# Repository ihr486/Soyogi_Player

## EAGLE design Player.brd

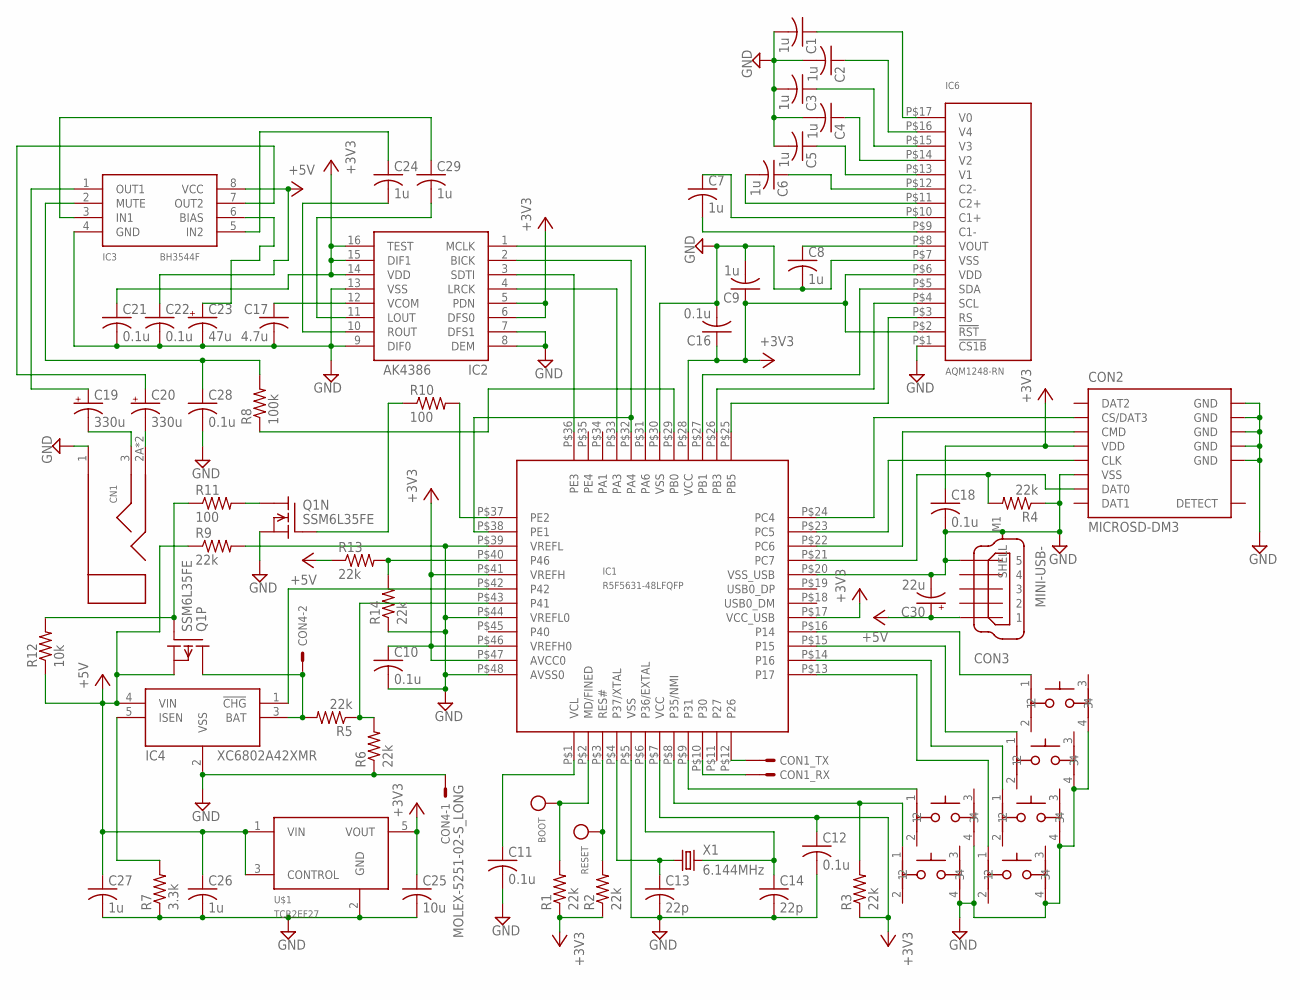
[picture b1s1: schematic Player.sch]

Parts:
BOOT: CHECK_PIN; SLC-22-G
C1, C2, C3, C4, C5, C6, C7, C8, C9, C24, C26, C27, C29: 1u; 2012-C
C10, C11, C12, C16, C18, C21, C22, C28: 0.1u; 2012-C
C13, C14: 22p; 1608
C17: 4.7u; 2012-C
C19, C20: 330u; E2,5-8
C23: 47u; E2,5-8
C25: 10u; 3216
C30: 22u; E2,5-8
CN1: STEREO-3.5-MJ8435; MJ8435
CON1: UART-S; IL-G-04-S
CON2: MICROSD-DM3; DM3AT-SF-PEJ
CON3: MINI-USB-; UX60A-MB-5ST
CON4: MOLEX-5251-02-S_LONG; 5251-02-S_LONG
IC1: R5F5631-48LFQFP; P-LFQFP48-7X7-0.50
IC2: AK4386; TSSOP16
IC3: BH3544F; SOIC8
IC4: XC6802A42XMR; SOT23-5
IC6: AQM1248-RN; AQM1248A-RN
Q1: SSM6L35FE; 2-2N1D
R1, R2, R3, R4, R5, R6, R9, R13, R14: 22k; 2012-R
R7: 3.3k; 2012-R
R8: 100k; 2012-R
R10, R11: 100; 2012-R
R12: 10k; 2012-R
RESET: CHECK_PIN; SLC-22-G
SW1, SW2, SW3, SW4, SW5, SW6: PUSHSW
U$1: TCR2EF27; 5-LEAD_TSOT
X1: 6.144MHz; TINYCRYSTAL

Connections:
+3V3: C9.1, C10.1, C12.1, C16.1, C18.1, C21.1, C25.1, CON2.4 (VDD), IC1.P$7 (VCC), IC1.P$17 (VCC_USB), IC1.P$28 (VCC), IC1.P$41 (VREFH), IC1.P$46 (VREFH0), IC1.P$47 (AVCC0), IC2.5 (PDN), IC2.6 (DFS0), IC2.14 (VDD), IC2.15 (DIF1), IC2.16 (TEST), IC6.P$2 (!RST), IC6.P$6 (VDD), R1.1, R2.1, R3.1, U$1.5 (VOUT)
+5V: C22.1, C26.1, C27.1, C30.+, CON3.1, IC3.8 (VCC), IC4.4 (VIN), Q1.4 (S), R9.1, R12.1, R13.1, U$1.1 (VIN), U$1.3 (CONTROL)
GND: C1.2, C2.2, C3.2, C4.2, C5.2, C8.2, C9.2, C10.2, C11.2, C12.2, C13.2, C14.2, C16.2, C17.2, C18.2, C21.2, C22.2, C23.-, C25.2, C26.2, C27.2, C28.2, C30.-, CN1.1 (SLEEVE), CON1.1 (GND), CON2.6 (VSS), CON2.SHELL1 (GND), CON2.SHELL2 (GND), CON2.SHELL3 (GND), CON2.SHELL4 (GND), CON2.SHELL5 (GND), CON3.5, CON3.M1 (SHELL), CON4.1, IC1.P$5 (VSS), IC1.P$20 (VSS_USB), IC1.P$30 (VSS), IC1.P$39 (VREFL), IC1.P$44 (VREFL0), IC1.P$48 (AVSS0), IC2.7 (DFS1), IC2.8 (DEM), IC2.9 (DIF0), IC2.13 (VSS), IC3.4 (GND), IC4.2 (VSS), IC6.P$1 (!CS1B), IC6.P$7 (VSS), Q1.1 (S), R4.1, R6.1, R7.1, R9.2, R14.1, SW1.4, SW2.4, SW3.4, SW4.4, SW5.4, SW6.4, U$1.2 (GND)
unnamed: C1.1, IC6.P$17 (V0)
unnamed: C2.1, IC6.P$16 (V4)
unnamed: C3.1, IC6.P$15 (V3)
unnamed: C4.1, IC6.P$14 (V2)
unnamed: C5.1, IC6.P$13 (V1)
unnamed: C11.1, IC1.P$1 (VCL)
unnamed: C6.1, IC6.P$12 (C2-)
unnamed: C6.2, IC6.P$11 (C2+)
unnamed: C7.1, IC6.P$10 (C1+)
unnamed: C7.2, IC6.P$9 (C1-)
unnamed: C8.1, IC6.P$8 (VOUT)
unnamed: CON1.3 (S), IC1.P$12 (P26)
unnamed: CON1.2 (S), IC1.P$10 (P30)
unnamed: IC1.P$9 (P31), SW2.1
unnamed: IC1.P$8 (P35/NMI), R3.2, SW1.1
unnamed: CON2.5 (CLK), IC1.P$23 (PC5)
unnamed: IC1.P$37 (PE2), R10.2
unnamed: Q1.2 (G), R10.1
unnamed: IC1.P$3 (RES#), R2.2, RESET.SIGNAL
unnamed: Q1.5 (G), R11.1, R12.2
unnamed: CON2.7 (DAT0), IC1.P$21 (PC7), R4.2
unnamed: BOOT.SIGNAL, IC1.P$2 (MD/FINED), R1.2
unnamed: IC1.P$16 (P14), SW6.1
unnamed: IC1.P$15 (P15), SW5.1
unnamed: IC1.P$14 (P16), SW4.1
unnamed: IC1.P$13 (P17), SW3.1
unnamed: CON2.3 (CMD), IC1.P$22 (PC6)
unnamed: CON2.2 (CS/DAT3), IC1.P$24 (PC4)
unnamed: C17.1, IC2.12 (VCOM)
unnamed: IC1.P$25 (PB5), IC6.P$3 (RS)
unnamed: IC1.P$26 (PB3), IC6.P$4 (SCL)
unnamed: IC1.P$27 (PB1), IC6.P$5 (SDA)
unnamed: C24.2, IC2.10 (ROUT)
unnamed: C29.2, IC2.11 (LOUT)
unnamed: C20.+, IC3.7 (OUT2)
unnamed: C23.+, IC3.6 (BIAS)
unnamed: C19.+, IC3.1 (OUT1)
unnamed: C19.-, CN1.3 (RING)
unnamed: C20.-, CN1.2A (TIP), CN1.2B (TIP)
unnamed: IC1.P$36 (PE3), IC2.3 (SDTI)
unnamed: IC1.P$31 (PA6), IC2.1 (MCLK)
unnamed: IC1.P$32 (PA4), IC1.P$38 (PE1), IC2.2 (BICK)
unnamed: IC1.P$33 (PA3), IC2.4 (LRCK)
unnamed: C24.1, IC3.5 (IN2)
unnamed: Q1.6 (D), R11.2
unnamed: IC1.P$43 (P41), R5.1, R6.2
unnamed: IC1.P$42 (P42), IC4.1 (!CHG!)
unnamed: CON4.2, IC4.3 (BAT), Q1.3 (D), R5.2
unnamed: C29.1, IC3.3 (IN1)
unnamed: IC4.5 (ISEN), R7.2
unnamed: C28.1, IC3.2 (MUTE), R8.2
unnamed: IC1.P$29 (PB0), R8.1
unnamed: IC1.P$40 (P46), R13.2, R14.2
unnamed: C13.1, IC1.P$4 (P37/XTAL), X1.1
unnamed: C14.1, IC1.P$6 (P36/EXTAL), X1.2
VCC: CON1.4 (VCC)

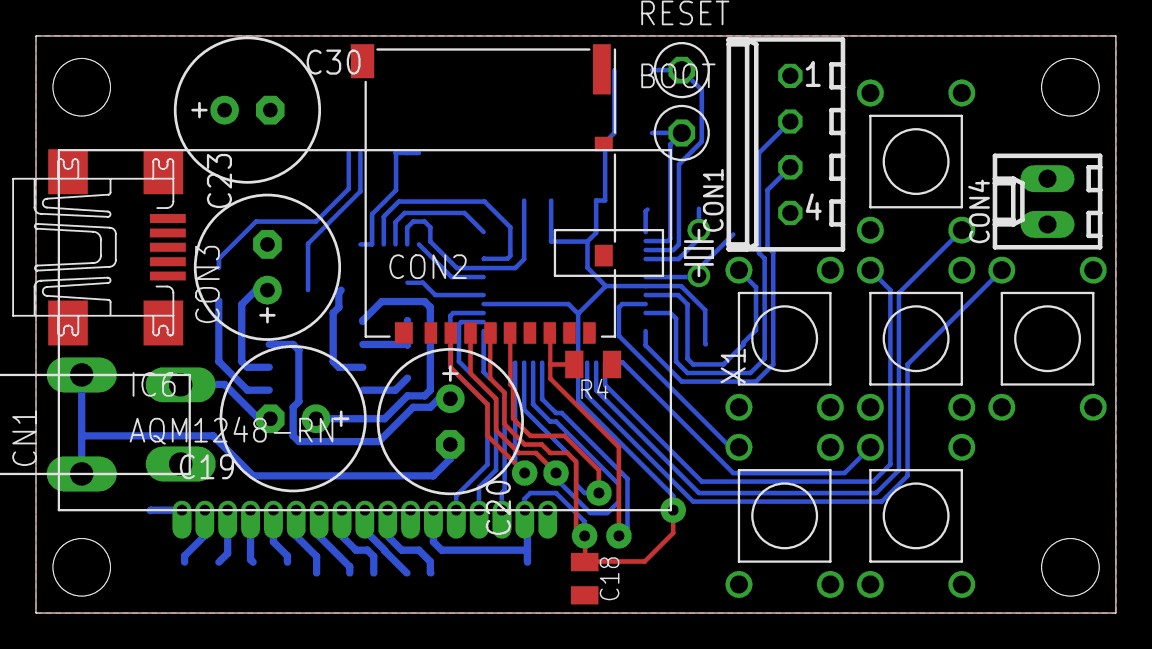
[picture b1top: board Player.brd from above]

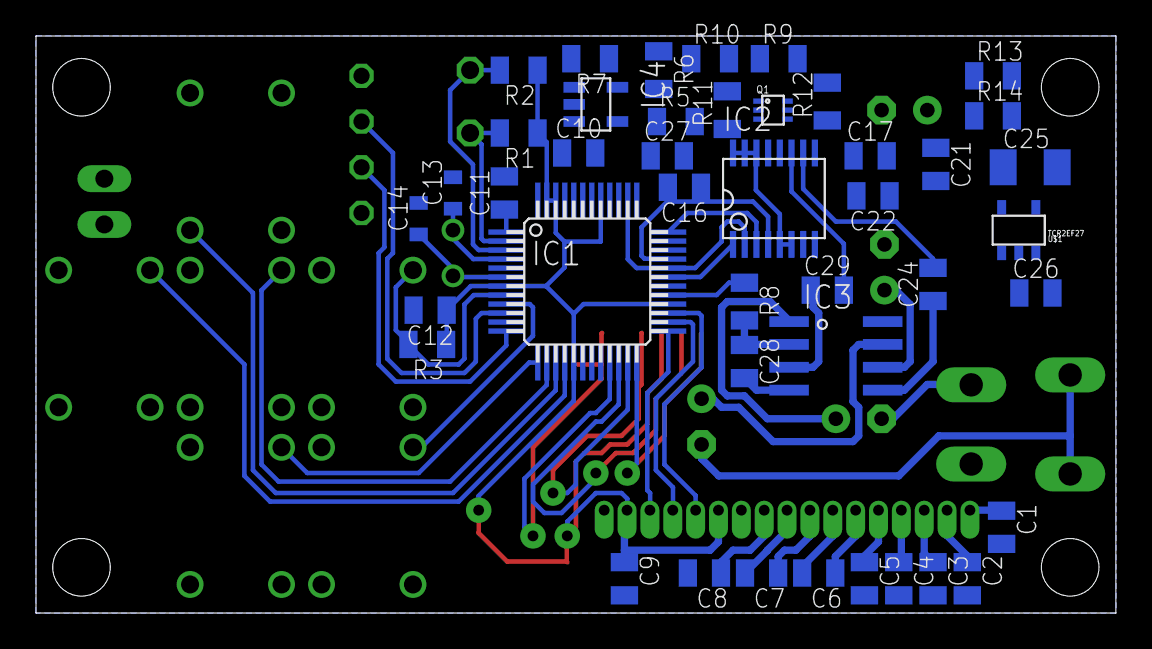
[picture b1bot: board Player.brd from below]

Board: 2 copper layers, 60.0 x 32.1 mm, 64 parts (43 on the bottom side), 58 nets.

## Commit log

2016-01-18 Halfway through wiring
